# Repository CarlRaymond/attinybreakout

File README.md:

# attinybreakout
A small breakout board for ATTiny85 with programming pads

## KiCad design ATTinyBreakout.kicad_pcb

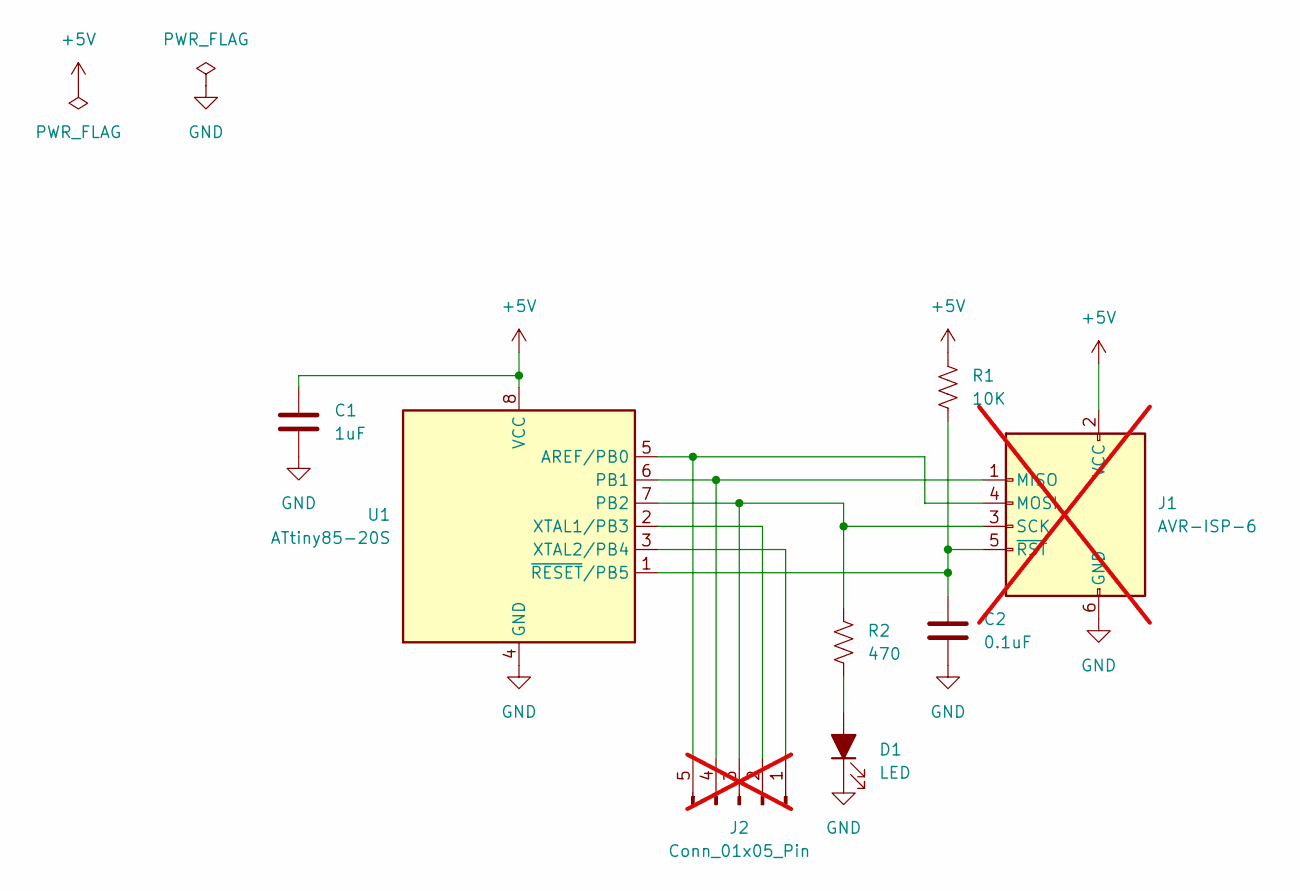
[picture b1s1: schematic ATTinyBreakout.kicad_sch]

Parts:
C1: 1uF; C_0805_2012Metric_Pad1.18x1.45mm_HandSolder
C2: 0.1uF; C_0805_2012Metric_Pad1.18x1.45mm_HandSolder
D1: LED; LED_0805_2012Metric
J1: AVR-ISP-6; PinHeader_2x03_P2.54mm_Vertical; not fitted
J2: Conn_01x05_Pin; PinHeader_1x05_P2.00mm_Vertical; not fitted
R1: 10K; R_0805_2012Metric_Pad1.20x1.40mm_HandSolder
R2: 470; R_0805_2012Metric_Pad1.20x1.40mm_HandSolder
U1: ATtiny85-20S; SOIC-8W_5.3x5.3mm_P1.27mm

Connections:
+5V: C1.1, J1.2 (VCC), R1.1, U1.8 (VCC)
GND: C1.2, C2.2, D1.1 (K), J1.6 (GND), U1.4 (GND)
unnamed: D1.2 (A), R2.2
unnamed: J1.1 (MISO), J2.4, U1.6 (PB1)
unnamed: J1.4 (MOSI), J2.5, U1.5 (AREF/PB0)
unnamed: J1.3 (SCK), J2.3, R2.1, U1.7 (PB2)
unnamed: C2.1, J1.5 (~RST), R1.2, U1.1 (~RESET/PB5)
unnamed: J2.1, U1.3 (XTAL2/PB4)
unnamed: J2.2, U1.2 (XTAL1/PB3)

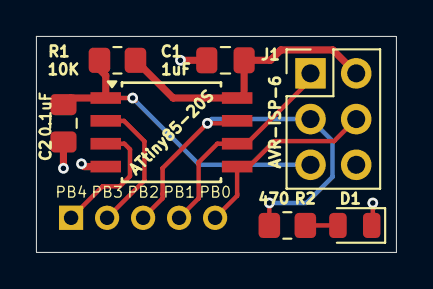
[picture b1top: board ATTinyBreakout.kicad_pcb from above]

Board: 2 copper layers, 20.0 x 12.0 mm, 8 parts (0 on the bottom side), 9 nets.

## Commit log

2025-03-02 Schematic and board
